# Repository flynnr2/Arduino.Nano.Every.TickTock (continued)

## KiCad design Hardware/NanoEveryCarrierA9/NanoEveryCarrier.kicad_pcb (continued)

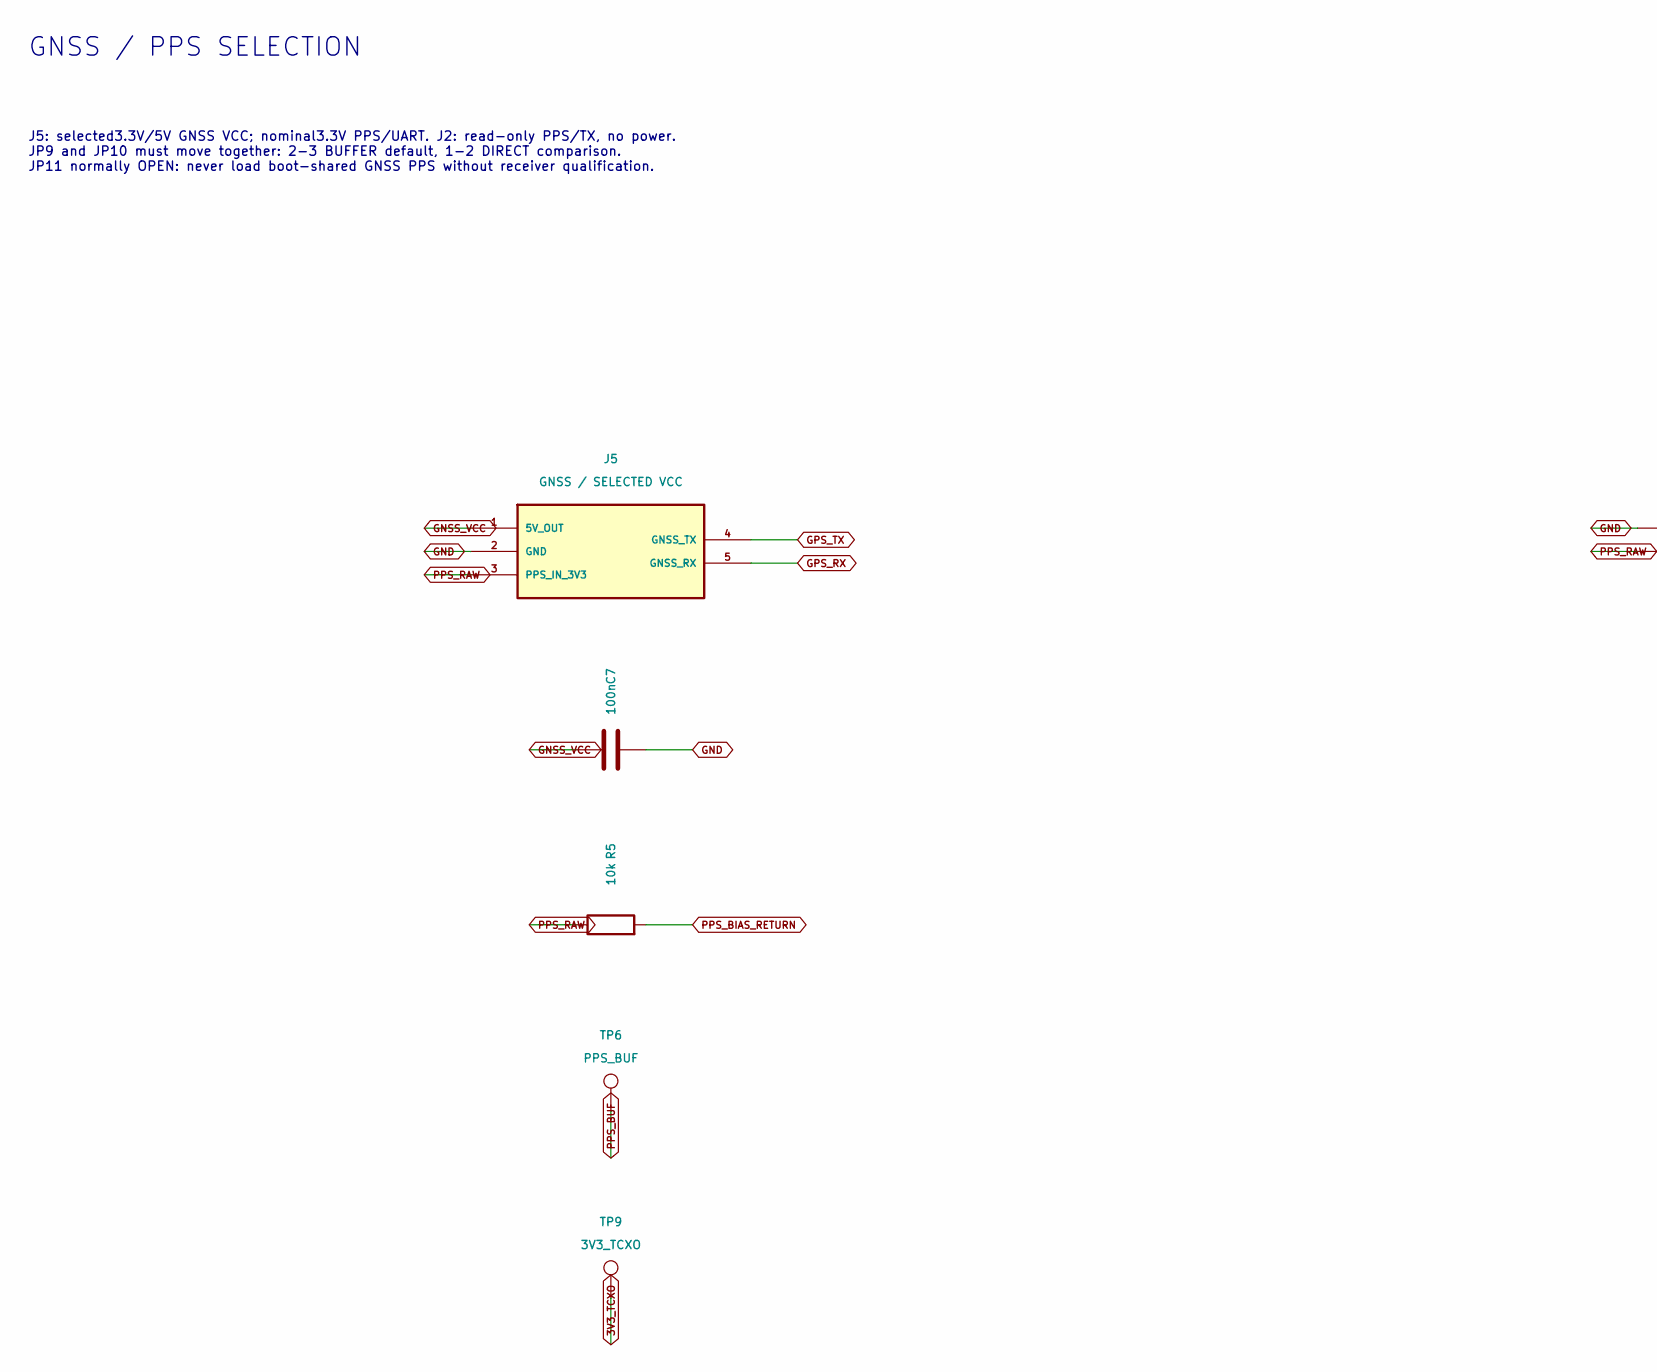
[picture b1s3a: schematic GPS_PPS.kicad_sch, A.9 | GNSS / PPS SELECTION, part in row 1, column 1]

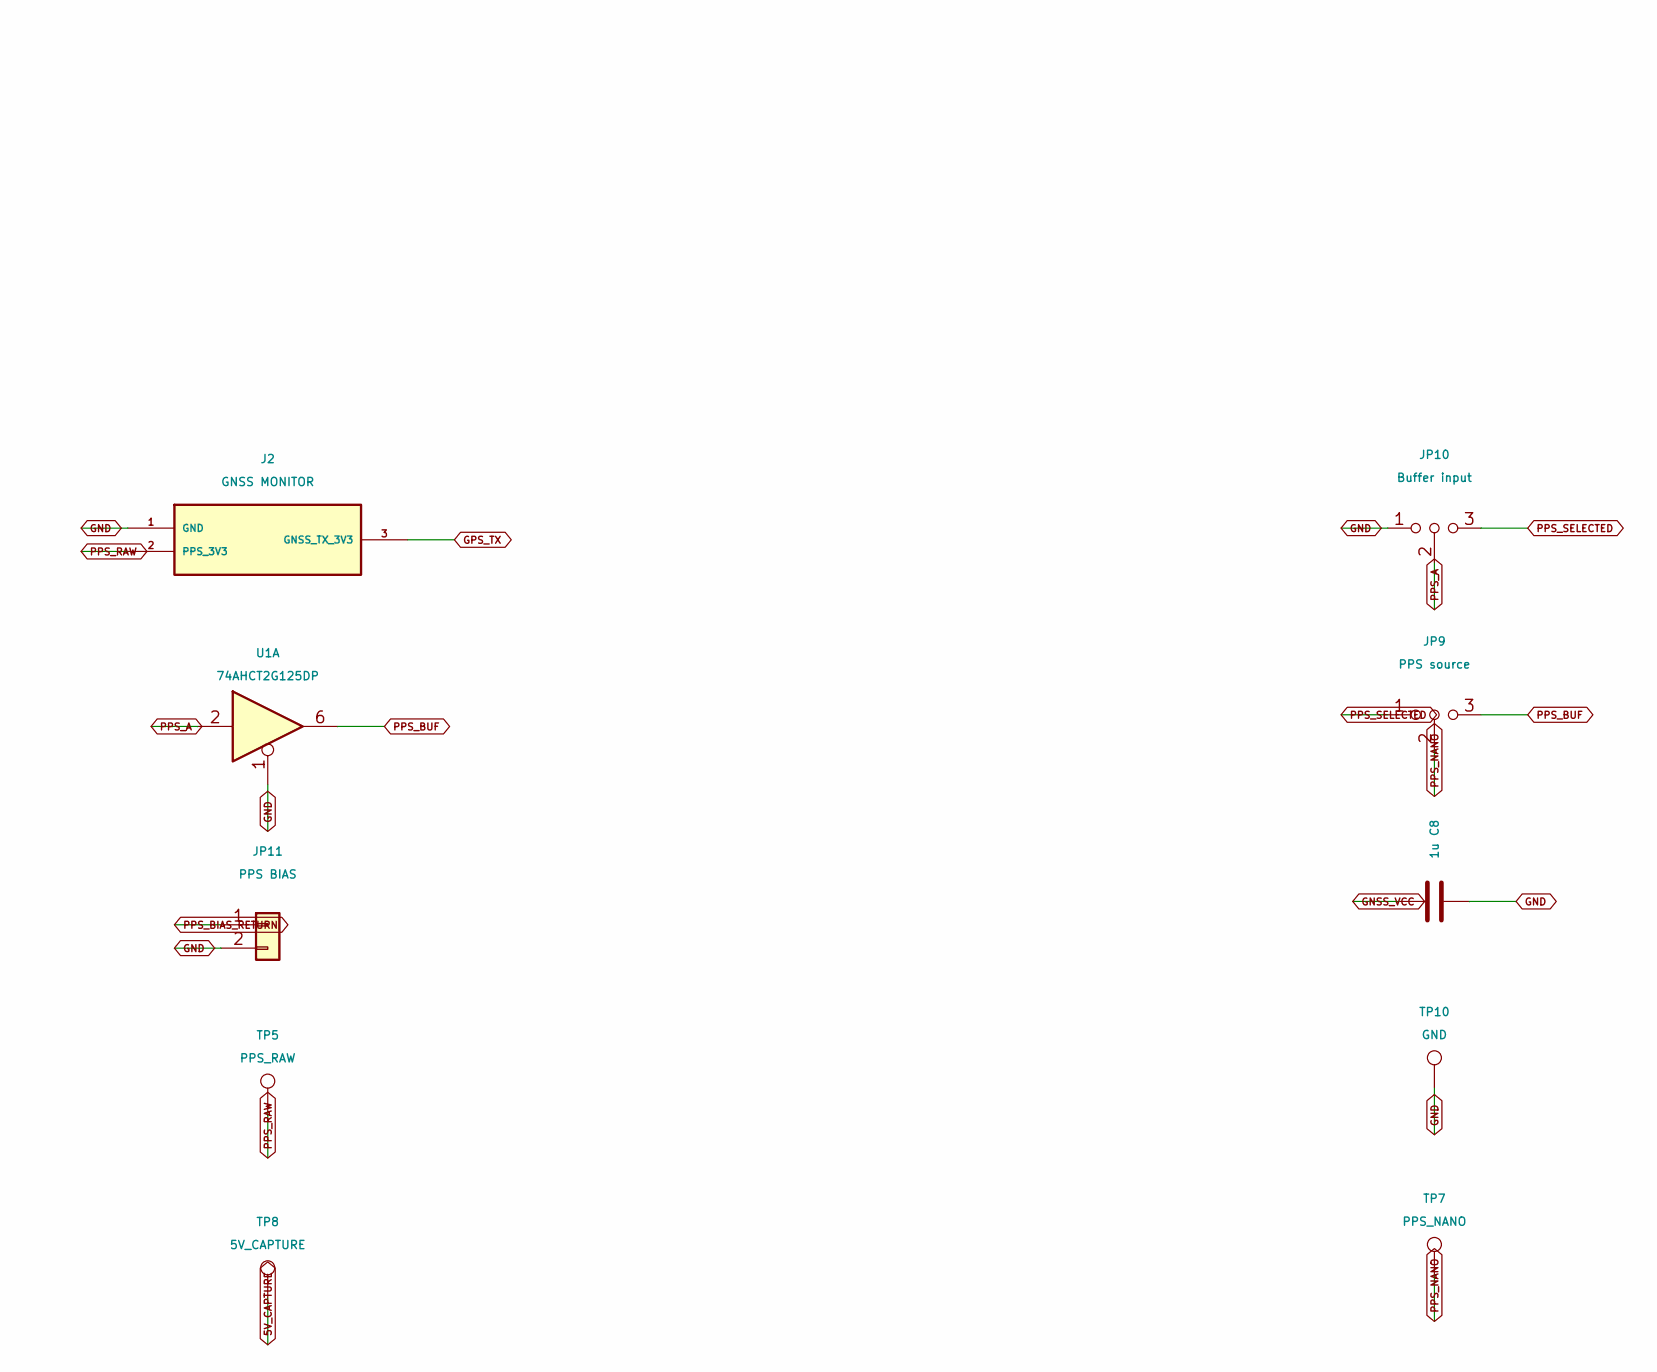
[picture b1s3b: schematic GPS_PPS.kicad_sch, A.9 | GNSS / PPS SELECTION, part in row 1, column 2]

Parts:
C7: 100n; C_0805_2012Metric; MPN GRM21BR71H104KA01L
C8: 1u; C_0805_2012Metric; MPN GRM21BR71C105KA01L
J2: GNSS MONITOR; PinHeader_1x03_P2.54mm_Vertical; MPN TSW-103-07-G-S
J5: GNSS / SELECTED VCC; PinHeader_1x05_P2.54mm_Vertical; MPN TSW-105-07-G-S
JP9: PPS source; PinHeader_1x03_P2.54mm_Vertical; MPN TSW-103-07-G-S
JP10: Buffer input; PinHeader_1x03_P2.54mm_Vertical; MPN TSW-103-07-G-S
JP11: PPS BIAS; PinHeader_1x02_P2.54mm_Vertical; MPN TSW-102-07-G-S
R5: 10k; R_0805_2012Metric; MPN RC0805FR-0710KL
TP5: PPS_RAW; TestPoint_Pad_D1.0mm
TP6: PPS_BUF; TestPoint_Pad_D1.0mm
TP7: PPS_NANO; TestPoint_Pad_D1.0mm
TP8: 5V_CAPTURE; TestPoint_Pad_D1.0mm
TP9: 3V3_TCXO; TestPoint_Pad_D1.0mm
TP10: GND; TestPoint_Pad_D1.0mm
U1: 74AHCT2G125DP; TSSOP-8_3x3mm_P0.65mm; MPN 74AHCT2G125DP,125

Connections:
3V3_TCXO: TP9.1; also elsewhere on the board
5V_CAPTURE: TP8.1; also elsewhere on the board
GND: C7.2, C8.2, J2.1 (GND), J5.2 (GND), JP10.1 (A), JP11.2, TP10.1, U1.1; also elsewhere on the board
GNSS_VCC: C7.1, C8.1, J5.1 (5V_OUT); also elsewhere on the board
GPS_RX: J5.5 (GNSS_RX); also elsewhere on the board
GPS_TX: J2.3 (GNSS_TX_3V3), J5.4 (GNSS_TX); also elsewhere on the board
PPS_A: JP10.2 (C), U1.2
PPS_BIAS_RETURN: JP11.1, R5.2
PPS_BUF: JP9.3 (B), TP6.1, U1.6
PPS_NANO: JP9.2 (C), TP7.1; also elsewhere on the board
PPS_RAW: J2.2 (PPS_3V3), J5.3 (PPS_IN_3V3), R5.1, TP5.1; also elsewhere on the board
PPS_SELECTED: JP9.1 (A), JP10.3 (B); also elsewhere on the board

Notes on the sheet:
GNSS / PPS SELECTION
J5: selected3.3V/5V GNSS VCC; nominal3.3V PPS/UART. J2: read-only PPS/TX, no power. JP9 and JP10 must move together: 2-3 BUFFER default, 1-2 DIRECT comparison. JP11 normally OPEN: never load boot-shared GNSS PPS without receiver qualification.

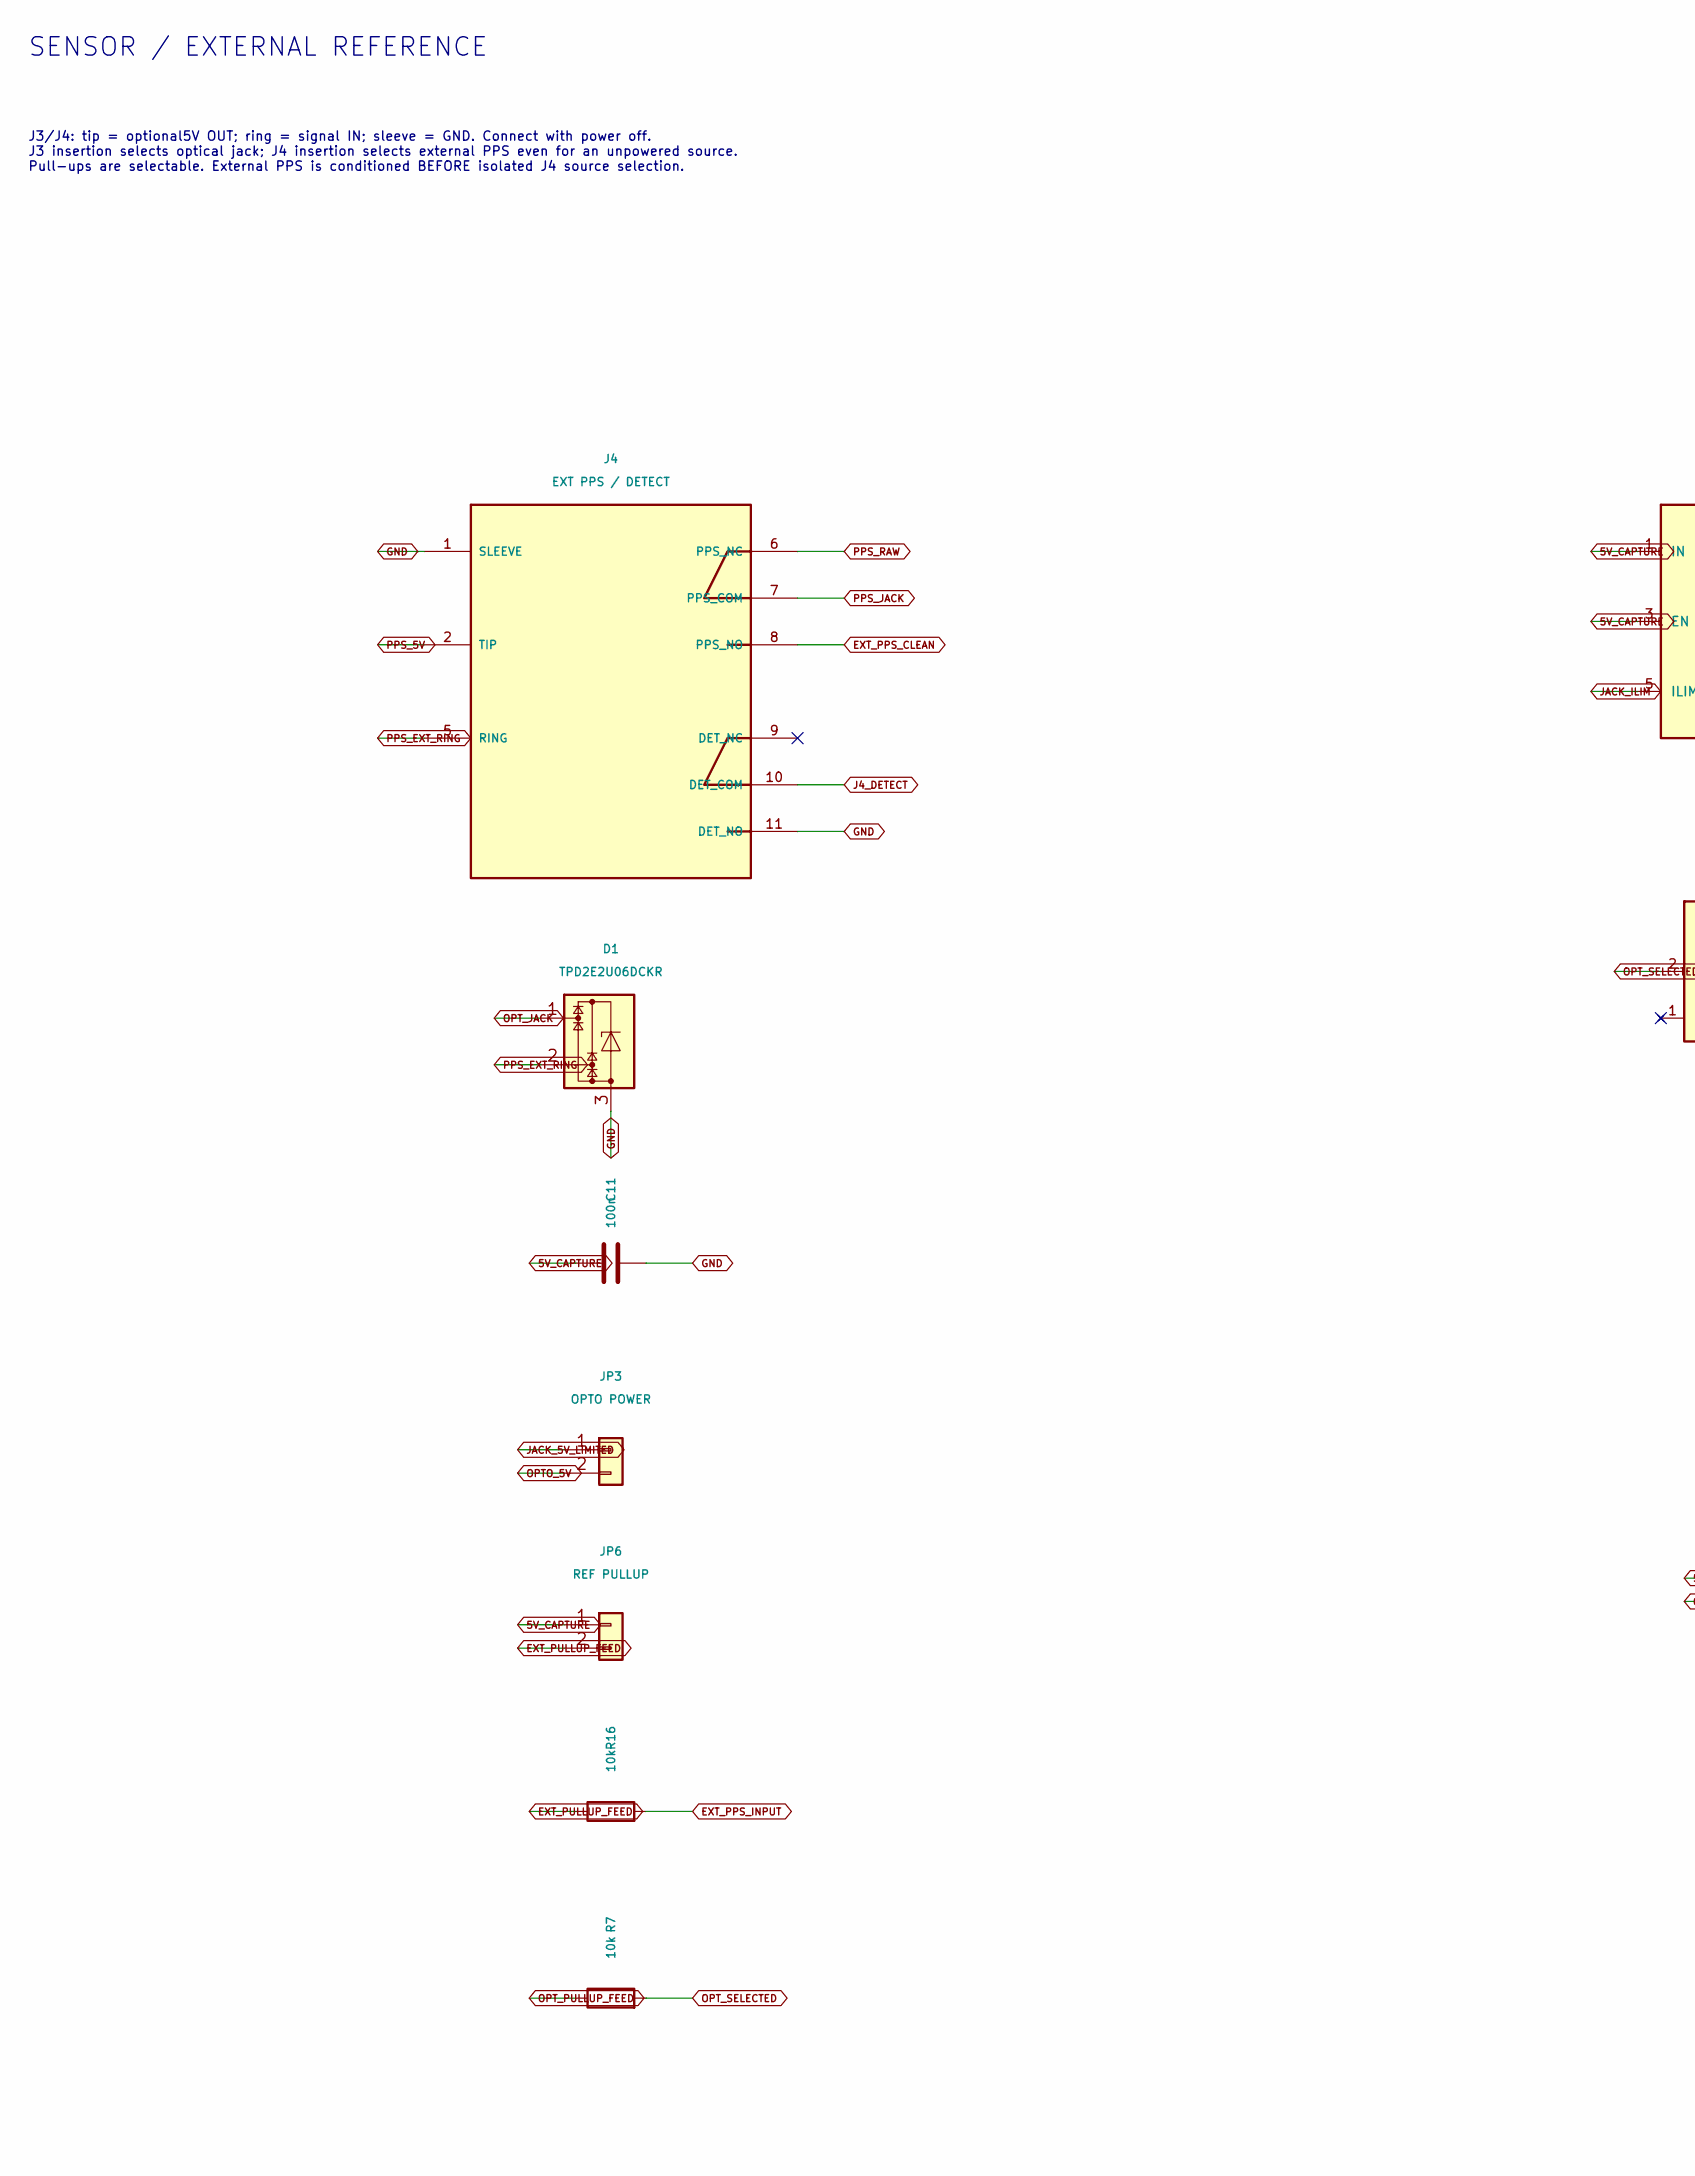
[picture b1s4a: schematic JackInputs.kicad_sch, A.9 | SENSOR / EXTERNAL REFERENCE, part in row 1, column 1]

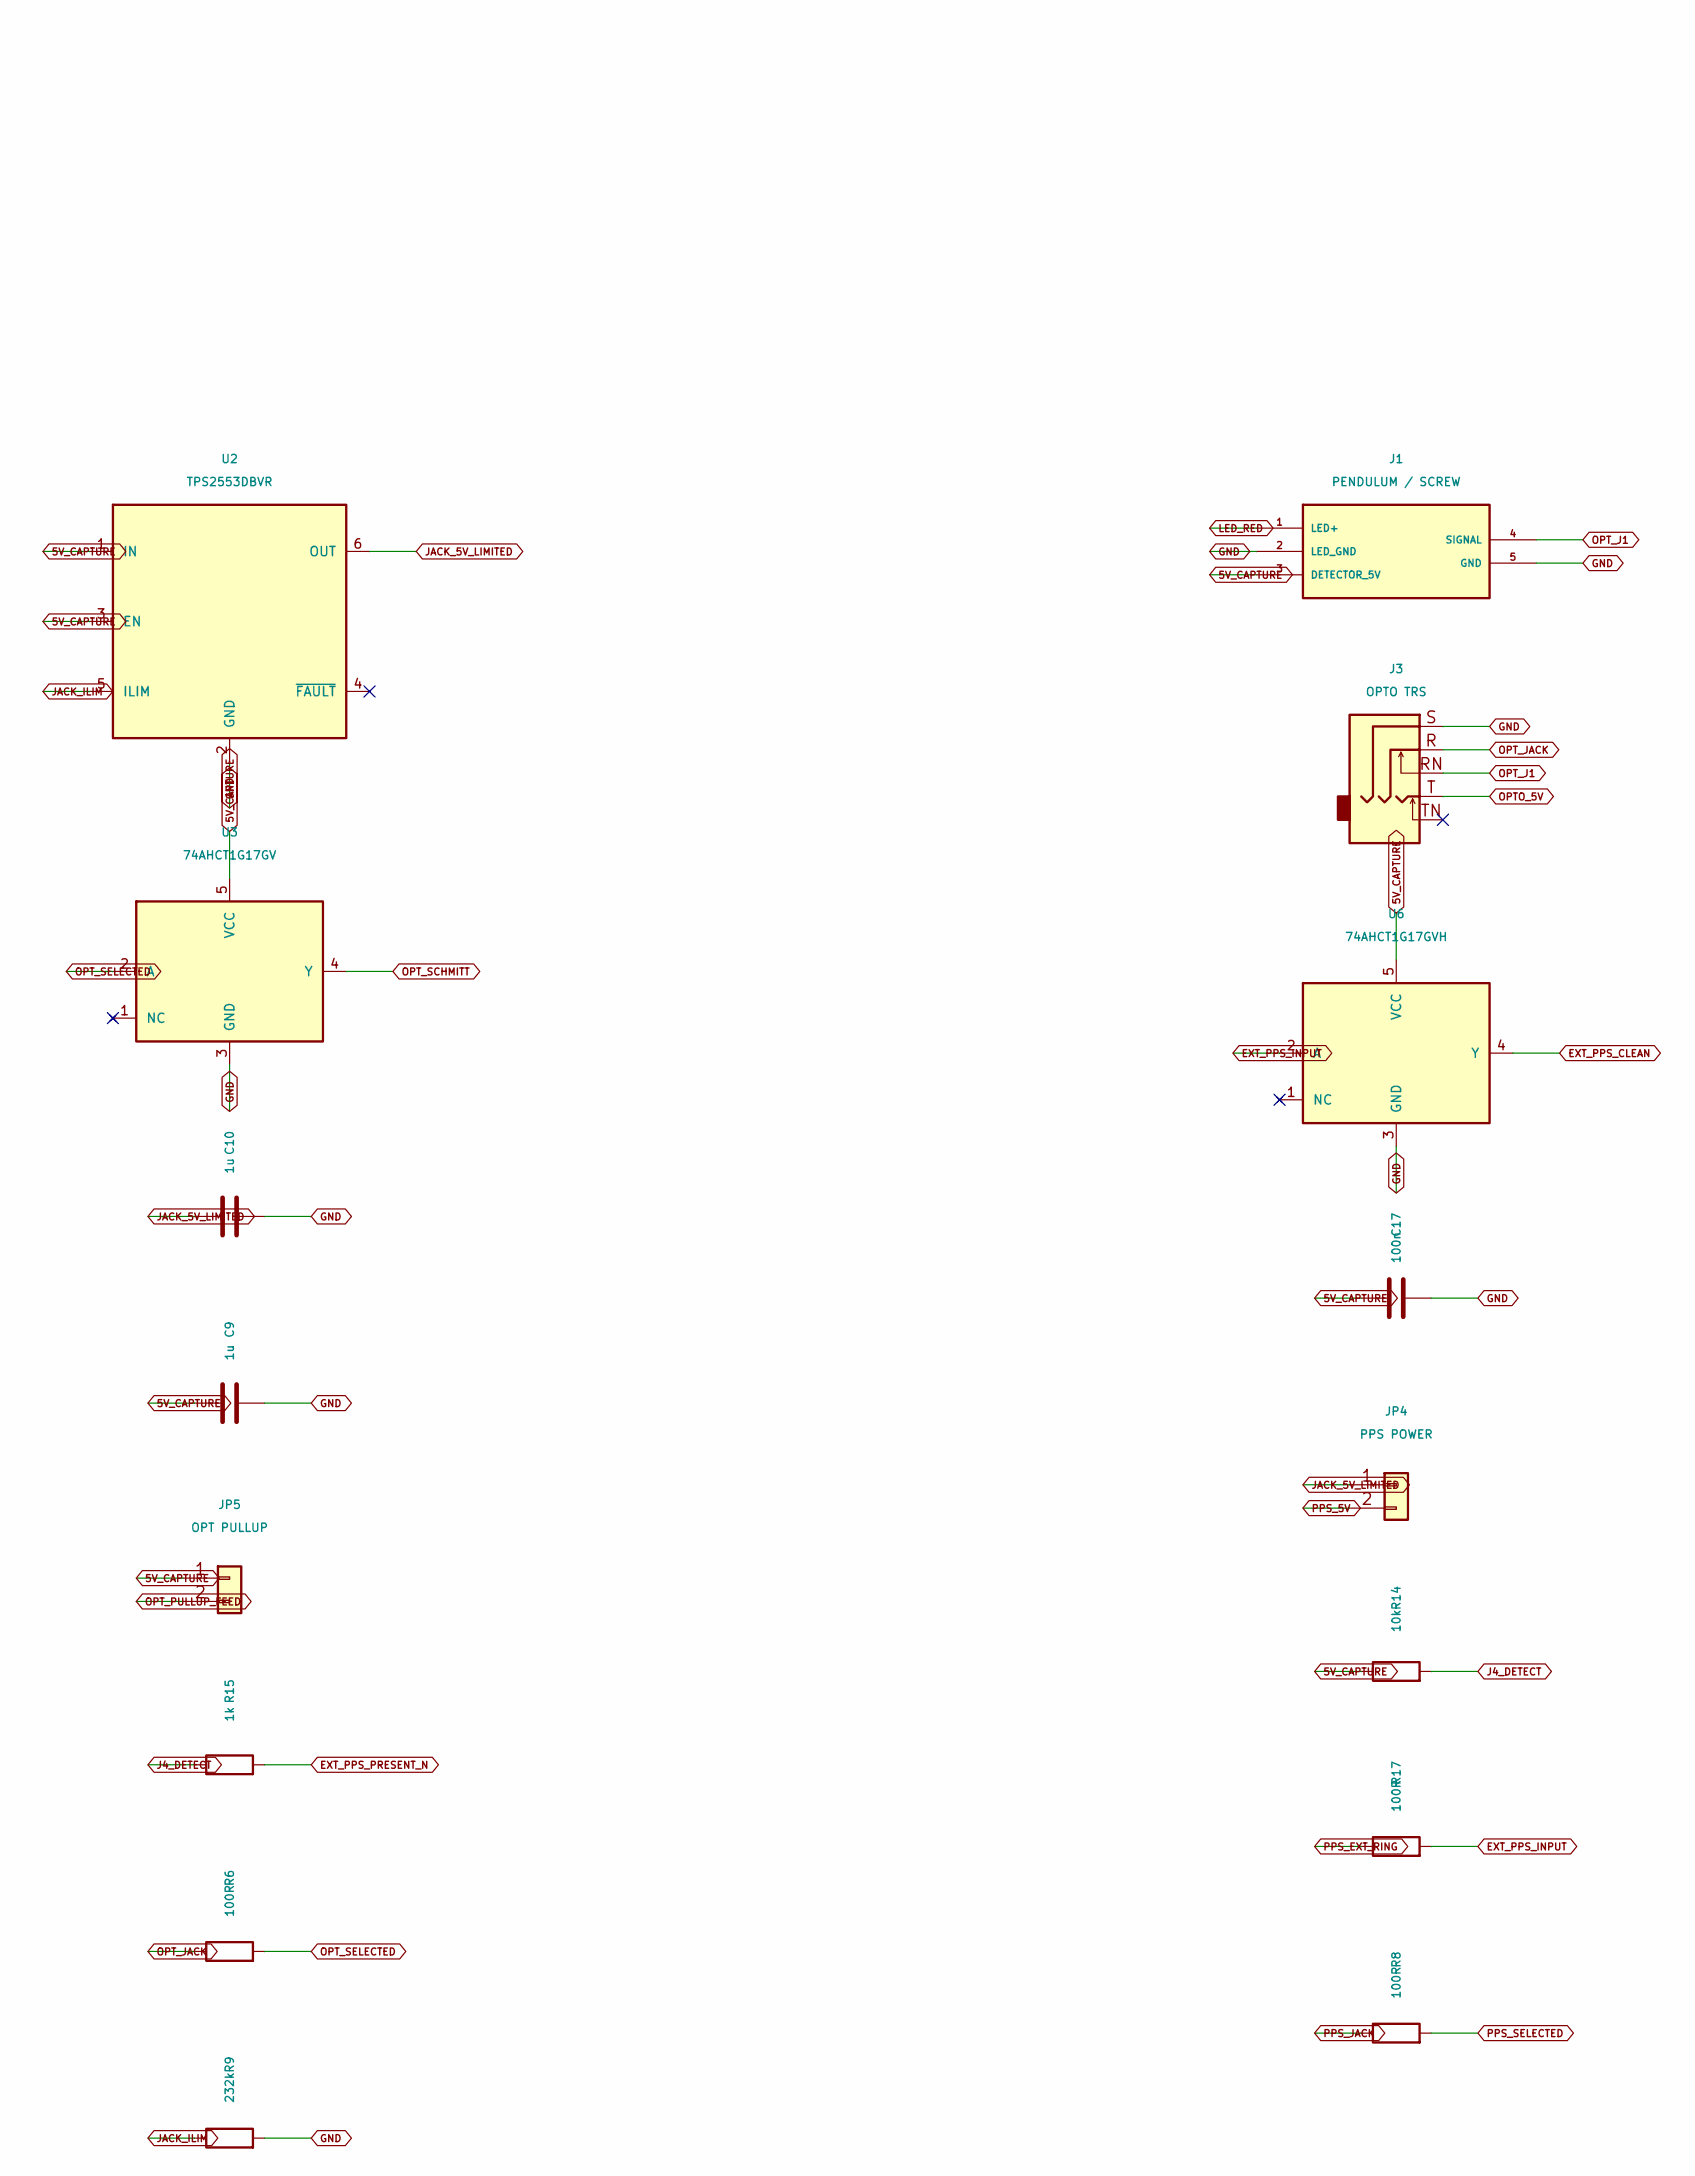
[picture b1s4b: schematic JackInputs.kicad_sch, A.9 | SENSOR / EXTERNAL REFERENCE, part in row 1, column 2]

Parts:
C9, C10: 1u; C_0805_2012Metric; MPN GRM21BR71C105KA01L
C11, C17: 100n; C_0805_2012Metric; MPN GRM21BR71H104KA01L
D1: TPD2E2U06DCKR; SOT-323_SC-70; MPN TPD2E2U06DCKR
J1: PENDULUM / SCREW; Wurth_691210910005; MPN 691210910005
J3: OPTO TRS; Jack_3.5mm_CUI_SJ1-3535NG_Horizontal_CircularHoles; MPN SJ1-3535NG
J4: EXT PPS / DETECT; Jack_3.5mm_Kycon_STX-3100-9N; MPN STX-3100-9N
JP3: OPTO POWER; PinHeader_1x02_P2.54mm_Vertical; MPN TSW-102-07-G-S
JP4: PPS POWER; PinHeader_1x02_P2.54mm_Vertical; MPN TSW-102-07-G-S
JP5: OPT PULLUP; PinHeader_1x02_P2.54mm_Vertical; MPN TSW-102-07-G-S
JP6: REF PULLUP; PinHeader_1x02_P2.54mm_Vertical; MPN TSW-102-07-G-S
R6, R8: 100R; R_1206_3216Metric_Pad1.30x1.75mm_HandSolder; MPN RC1206FR-07100RL
R7: 10k; R_1206_3216Metric_Pad1.30x1.75mm_HandSolder; MPN RC1206FR-0710KL
R9: 232k; R_0805_2012Metric; MPN RC0805FR-07232KL
R14, R16: 10k; R_0805_2012Metric; MPN RC0805FR-0710KL
R15: 1k; R_0805_2012Metric; MPN RC0805FR-071KL
R17: 100R; R_0805_2012Metric; MPN RC0805FR-07100RL
U2: TPS2553DBVR; SOT-23-6; MPN TPS2553DBVR
U3: 74AHCT1G17GV; SOT-23-5; MPN 74AHCT1G17GVH
U6: 74AHCT1G17GVH; SOT-23-5; MPN 74AHCT1G17GVH

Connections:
5V_CAPTURE: C9.1, C11.1, C17.1, J1.3 (DETECTOR_5V), JP5.1, JP6.1, R14.1, U2.1 (IN), U2.3 (EN), U3.5 (VCC), U6.5 (VCC); also elsewhere on the board
EXT_PPS_CLEAN: J4.8 (PPS_NO), U6.4 (Y)
EXT_PPS_INPUT: R16.2, R17.2, U6.2 (A)
EXT_PPS_PRESENT_N: R15.2; also elsewhere on the board
EXT_PULLUP_FEED: JP6.2, R16.1
GND: C9.2, C10.2, C11.2, C17.2, D1.3, J1.2 (LED_GND), J1.5 (GND), J3.S, J4.1 (SLEEVE), J4.11 (DET_NO), R9.2, U2.2 (GND), U3.3 (GND), U6.3 (GND); also elsewhere on the board
J4_DETECT: J4.10 (DET_COM), R14.2, R15.1
JACK_5V_LIMITED: C10.1, JP3.1, JP4.1, U2.6 (OUT)
JACK_ILIM: R9.1, U2.5 (ILIM)
LED_RED: J1.1 (LED+); also elsewhere on the board
OPTO_5V: J3.T, JP3.2
OPT_J1: J1.4 (SIGNAL), J3.RN
OPT_JACK: D1.1, J3.R, R6.1
OPT_PULLUP_FEED: JP5.2, R7.1
OPT_SCHMITT: U3.4 (Y); also elsewhere on the board
OPT_SELECTED: R6.2, R7.2, U3.2 (A); also elsewhere on the board
PPS_5V: J4.2 (TIP), JP4.2
PPS_EXT_RING: D1.2, J4.5 (RING), R17.1
PPS_JACK: J4.7 (PPS_COM), R8.1
PPS_RAW: J4.6 (PPS_NC); also elsewhere on the board
PPS_SELECTED: R8.2; also elsewhere on the board

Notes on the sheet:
SENSOR / EXTERNAL REFERENCE
J3/J4: tip = optional5V OUT; ring = signal IN; sleeve = GND. Connect with power off. J3 insertion selects optical jack; J4 insertion selects external PPS even for an unpowered source. Pull-ups are selectable. External PPS is conditioned BEFORE isolated J4 source selection.

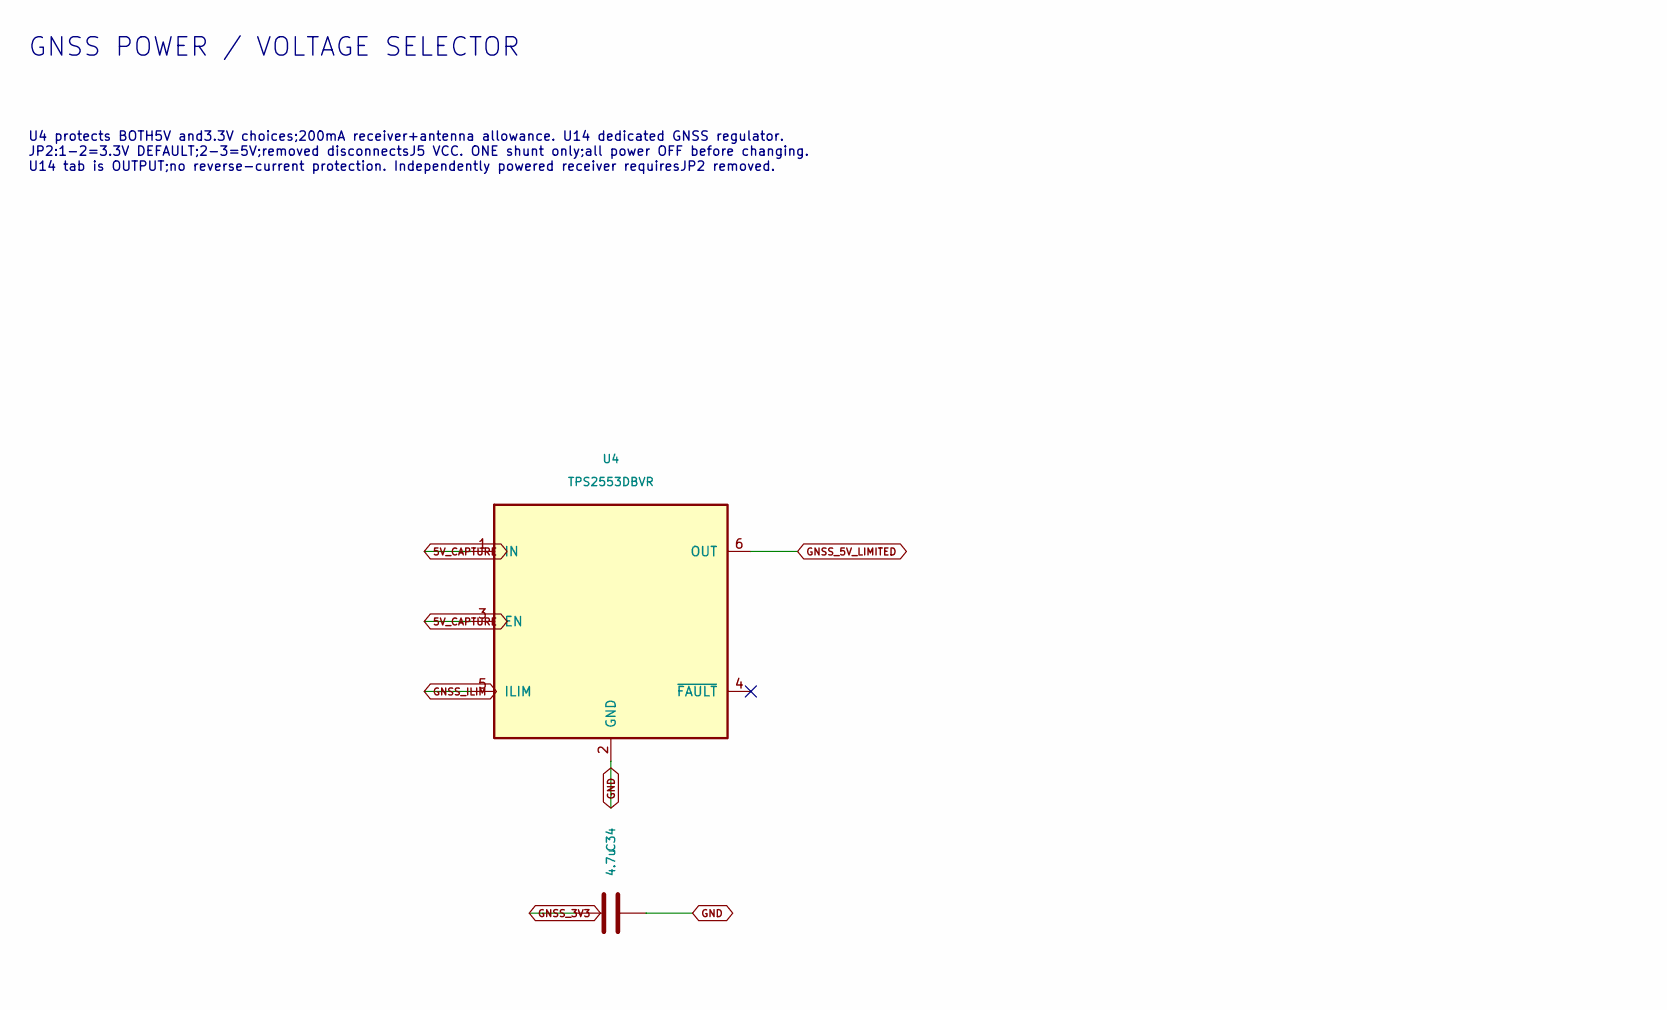
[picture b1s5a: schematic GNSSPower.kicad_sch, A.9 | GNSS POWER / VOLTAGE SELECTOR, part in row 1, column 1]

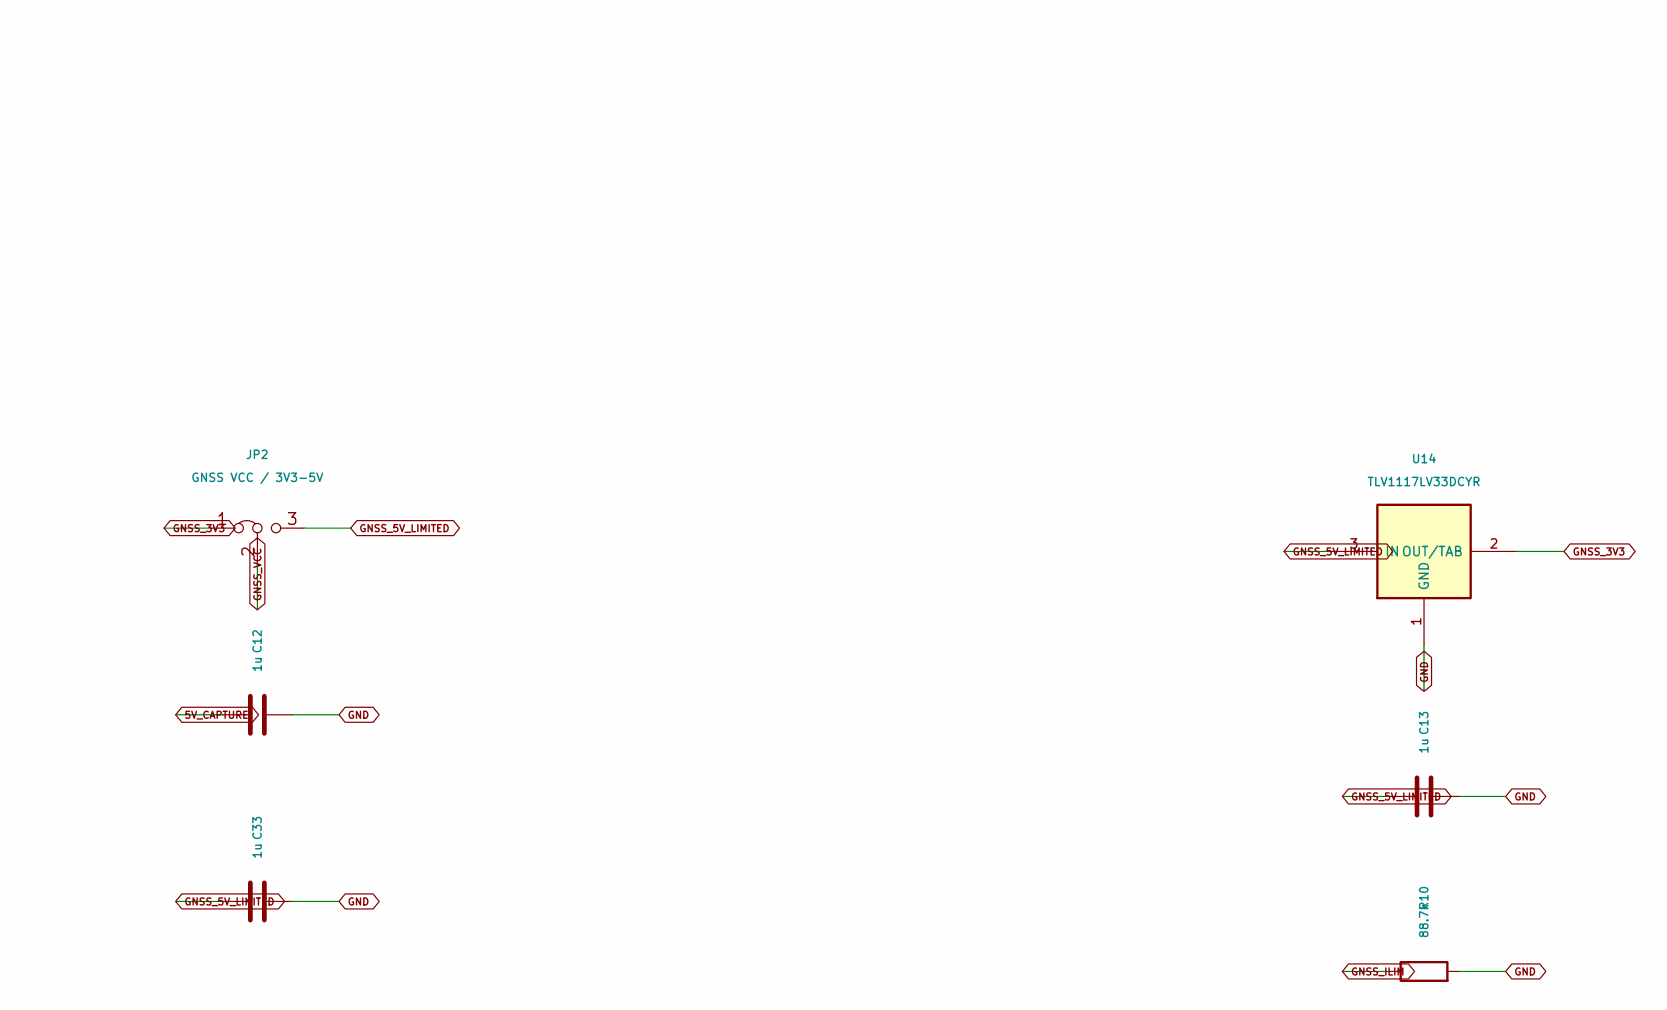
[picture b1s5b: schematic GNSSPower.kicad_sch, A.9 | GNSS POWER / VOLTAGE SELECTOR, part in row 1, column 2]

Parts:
C12, C13, C33: 1u; C_0805_2012Metric; MPN GRM21BR71C105KA01L
C34: 4.7u; C_0805_2012Metric; MPN GRM21BR71C475KA73L
JP2: GNSS VCC / 3V3-5V; PinHeader_1x03_P2.54mm_Vertical; MPN TSW-103-07-G-S
R10: 88.7k; R_0805_2012Metric; MPN RC0805FR-0788K7L
U4: TPS2553DBVR; SOT-23-6; MPN TPS2553DBVR
U14: TLV1117LV33DCYR; SOT-223-3_TabPin2; MPN TLV1117LV33DCYR

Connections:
5V_CAPTURE: C12.1, U4.1 (IN), U4.3 (EN); also elsewhere on the board
GND: C12.2, C13.2, C33.2, C34.2, R10.2, U4.2 (GND), U14.1 (GND); also elsewhere on the board
GNSS_3V3: C34.1, JP2.1 (A), U14.2 (OUT/TAB)
GNSS_5V_LIMITED: C13.1, C33.1, JP2.3 (B), U4.6 (OUT), U14.3 (IN)
GNSS_ILIM: R10.1, U4.5 (ILIM)
GNSS_VCC: JP2.2 (C); also elsewhere on the board

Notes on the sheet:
GNSS POWER / VOLTAGE SELECTOR
U4 protects BOTH5V and3.3V choices;200mA receiver+antenna allowance. U14 dedicated GNSS regulator. JP2:1-2=3.3V DEFAULT;2-3=5V;removed disconnectsJ5 VCC. ONE shunt only;all power OFF before changing. U14 tab is OUTPUT;no reverse-current protection. Independently powered receiver requiresJP2 removed.

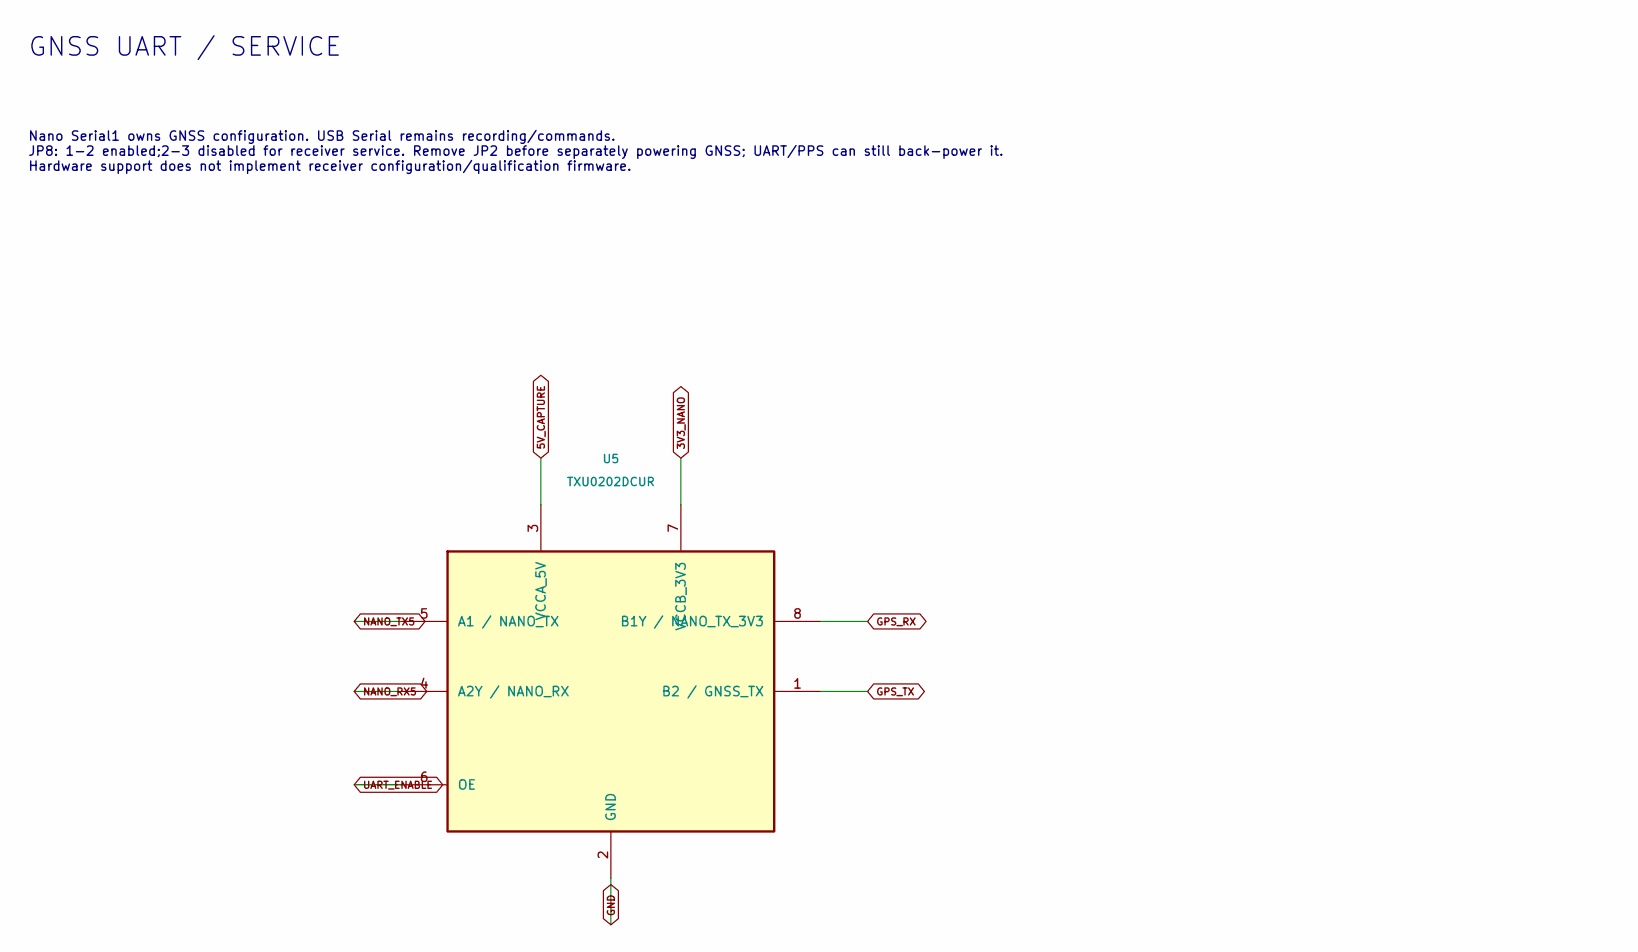
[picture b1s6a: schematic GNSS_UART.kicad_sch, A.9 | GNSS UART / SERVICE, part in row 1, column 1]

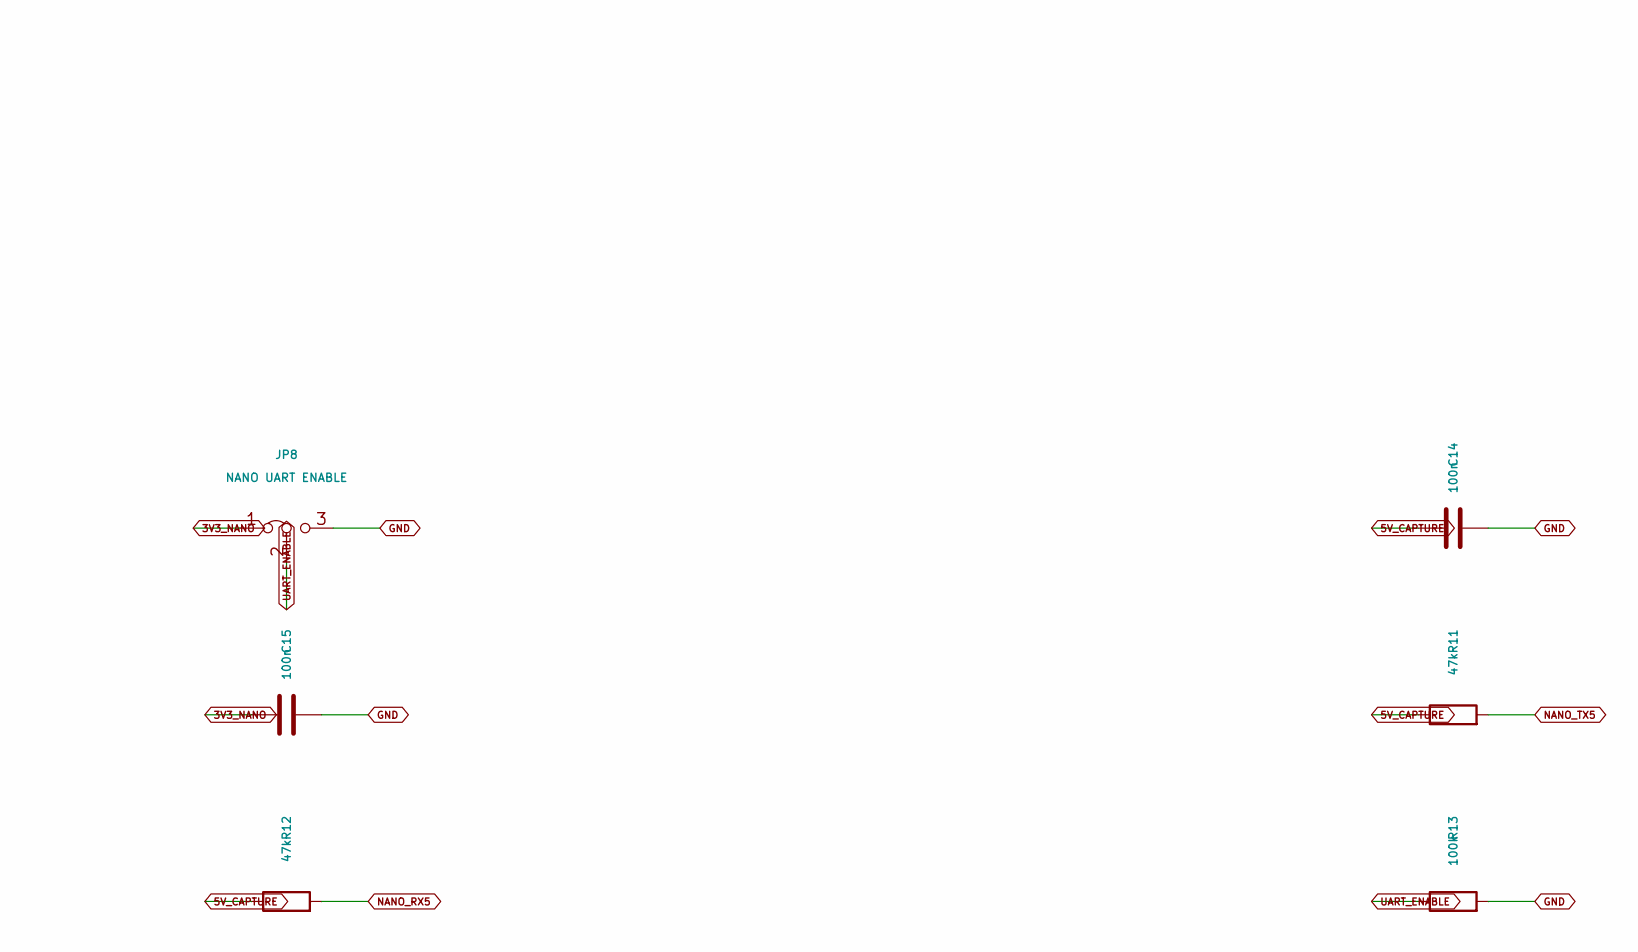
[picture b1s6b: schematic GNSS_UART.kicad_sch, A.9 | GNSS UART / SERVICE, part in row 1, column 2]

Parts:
C14, C15: 100n; C_0805_2012Metric; MPN GRM21BR71H104KA01L
JP8: NANO UART ENABLE; PinHeader_1x03_P2.54mm_Vertical; MPN TSW-103-07-G-S
R11, R12: 47k; R_0805_2012Metric; MPN RC0805FR-0747KL
R13: 100k; R_0805_2012Metric; MPN RC0805FR-07100KL
U5: TXU0202DCUR; TI_DCU0008A_VSSOP-8_2.3x2mm_P0.5mm; MPN TXU0202DCUR

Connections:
3V3_NANO: C15.1, JP8.1 (A), U5.7 (VCCB_3V3); also elsewhere on the board
5V_CAPTURE: C14.1, R11.1, R12.1, U5.3 (VCCA_5V); also elsewhere on the board
GND: C14.2, C15.2, JP8.3 (B), R13.2, U5.2 (GND); also elsewhere on the board
GPS_RX: U5.8 (B1Y / NANO_TX_3V3); also elsewhere on the board
GPS_TX: U5.1 (B2 / GNSS_TX); also elsewhere on the board
NANO_RX5: R12.2, U5.4 (A2Y / NANO_RX); also elsewhere on the board
NANO_TX5: R11.2, U5.5 (A1 / NANO_TX); also elsewhere on the board
UART_ENABLE: JP8.2 (C), R13.1, U5.6 (OE)

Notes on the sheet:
GNSS UART / SERVICE
Nano Serial1 owns GNSS configuration. USB Serial remains recording/commands. JP8: 1-2 enabled;2-3 disabled for receiver service. Remove JP2 before separately powering GNSS; UART/PPS can still back-power it. Hardware support does not implement receiver configuration/qualification firmware.
